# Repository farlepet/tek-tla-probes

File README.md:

Tektronix logic analyzer probes
===============================

This repo contains logic probes/leadsets for Tektronix logic analyzers, currently
specifically for the TLA 5200 series.

More details to come once I receive PCBs and build some probes.

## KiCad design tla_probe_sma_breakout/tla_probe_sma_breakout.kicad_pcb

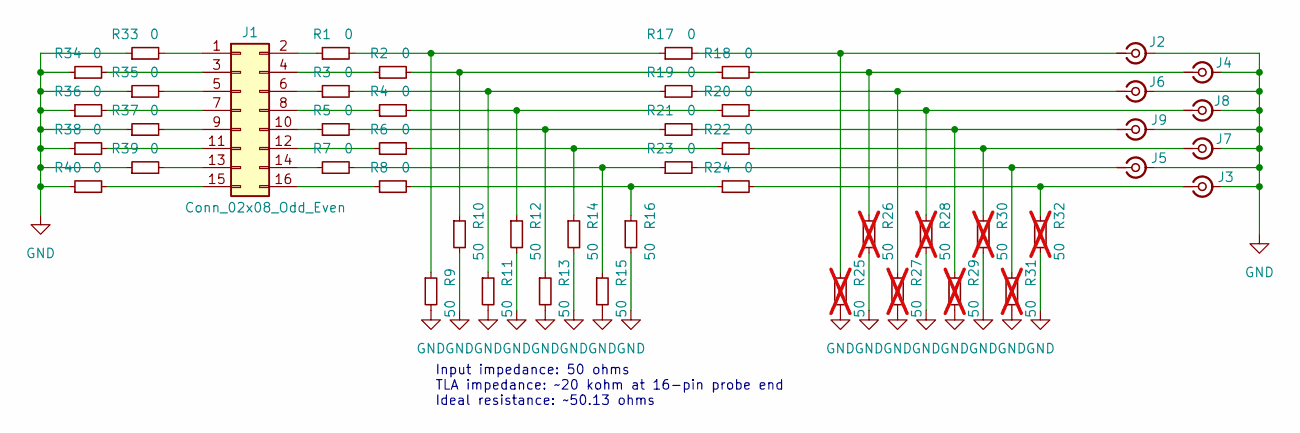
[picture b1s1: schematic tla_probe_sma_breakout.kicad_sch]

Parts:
J1: Conn_02x08_Odd_Even; PinHeader_2x08_P2.54mm_Vertical
J2, J3, J4, J5, J6, J7, J8, J9: Conn_Coaxial_Small; SMA Board Edge Jack
R1, R2, R3, R4, R5, R6, R7, R8, R17, R18, R19, R20, R21, R22, R23, R24, R33, R34, R35, R36, R37, R38, R39, R40: 0; R_0603_1608Metric
R9, R10, R11, R12, R13, R14, R15, R16: 50; R_0603_1608Metric
R25, R26, R27, R28, R29, R30, R31, R32: 50; R_0603_1608Metric; not fitted

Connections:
GND: J2.2 (Ext), J3.2 (Ext), J4.2 (Ext), J5.2 (Ext), J6.2 (Ext), J7.2 (Ext), J8.2 (Ext), J9.2 (Ext), R9.2, R10.2, R11.2, R12.2, R13.2, R14.2, R15.2, R16.2, R25.2, R26.2, R27.2, R28.2, R29.2, R30.2, R31.2, R32.2, R33.1, R34.1, R35.1, R36.1, R37.1, R38.1, R39.1, R40.1
unnamed: J1.1, R33.2
unnamed: J1.2, R1.1
unnamed: J1.3, R34.2
unnamed: J1.4, R2.1
unnamed: J1.5, R35.2
unnamed: J1.6, R3.1
unnamed: J1.7, R36.2
unnamed: J1.8, R4.1
unnamed: J1.9, R37.2
unnamed: J1.10, R5.1
unnamed: J1.11, R38.2
unnamed: J1.12, R6.1
unnamed: J1.13, R39.2
unnamed: J1.14, R7.1
unnamed: J1.15, R40.2
unnamed: J1.16, R8.1
unnamed: J2.1 (In), R17.2, R25.1
unnamed: J4.1 (In), R18.2, R26.1
unnamed: J6.1 (In), R19.2, R27.1
unnamed: J8.1 (In), R20.2, R28.1
unnamed: J9.1 (In), R21.2, R29.1
unnamed: J7.1 (In), R22.2, R30.1
unnamed: J5.1 (In), R23.2, R31.1
unnamed: J3.1 (In), R24.2, R32.1
unnamed: R1.2, R9.1, R17.1
unnamed: R2.2, R10.1, R18.1
unnamed: R3.2, R11.1, R19.1
unnamed: R4.2, R12.1, R20.1
unnamed: R5.2, R13.1, R21.1
unnamed: R6.2, R14.1, R22.1
unnamed: R7.2, R15.1, R23.1
unnamed: R8.2, R16.1, R24.1

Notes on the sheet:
Input impedance: 50 ohms TLA impedance: ~20 kohm at 16-pin probe end Ideal resistance: ~50.13 ohms

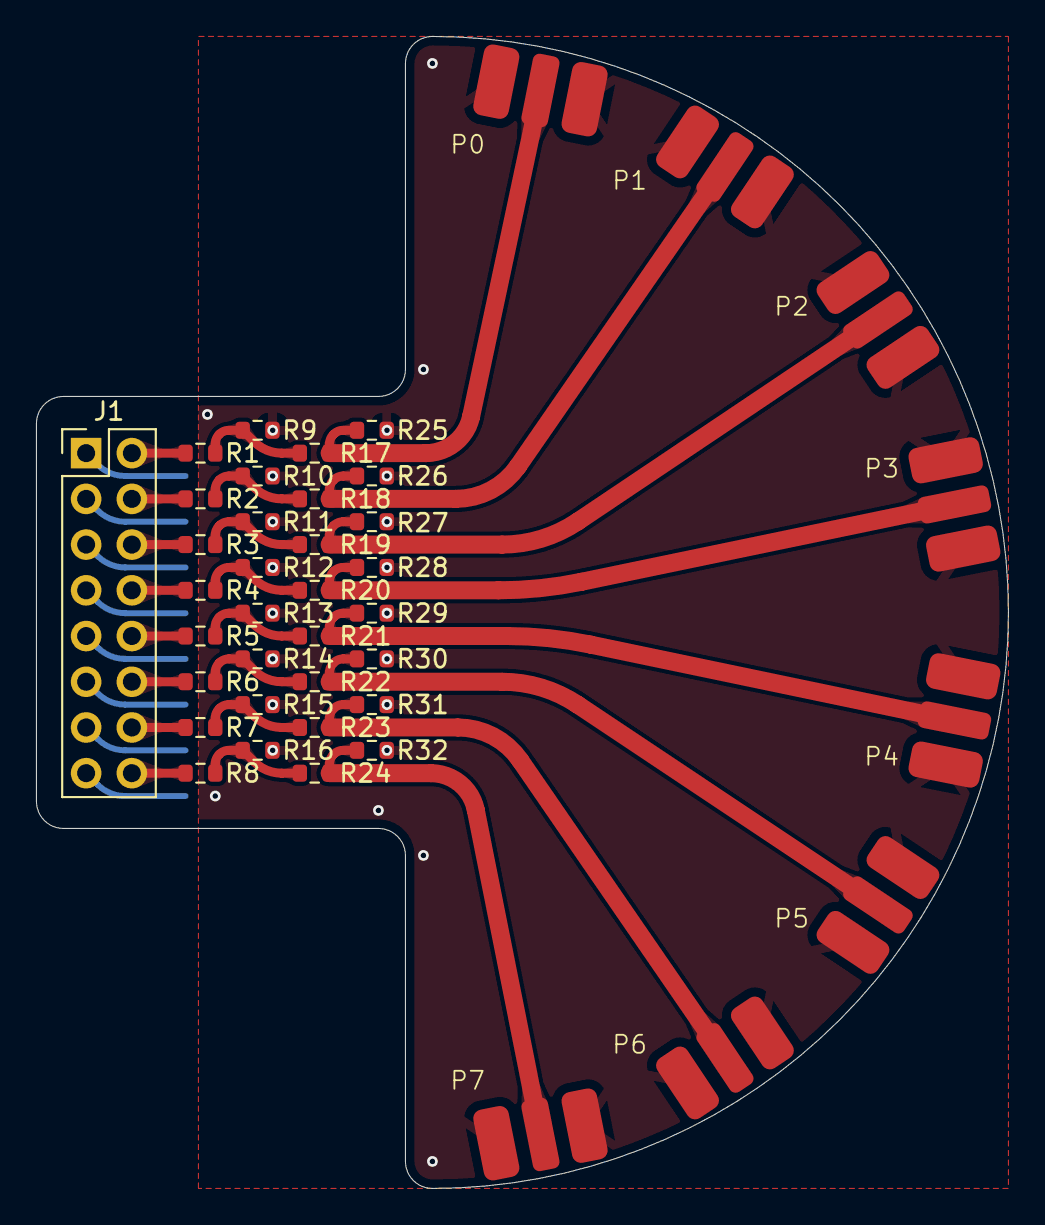
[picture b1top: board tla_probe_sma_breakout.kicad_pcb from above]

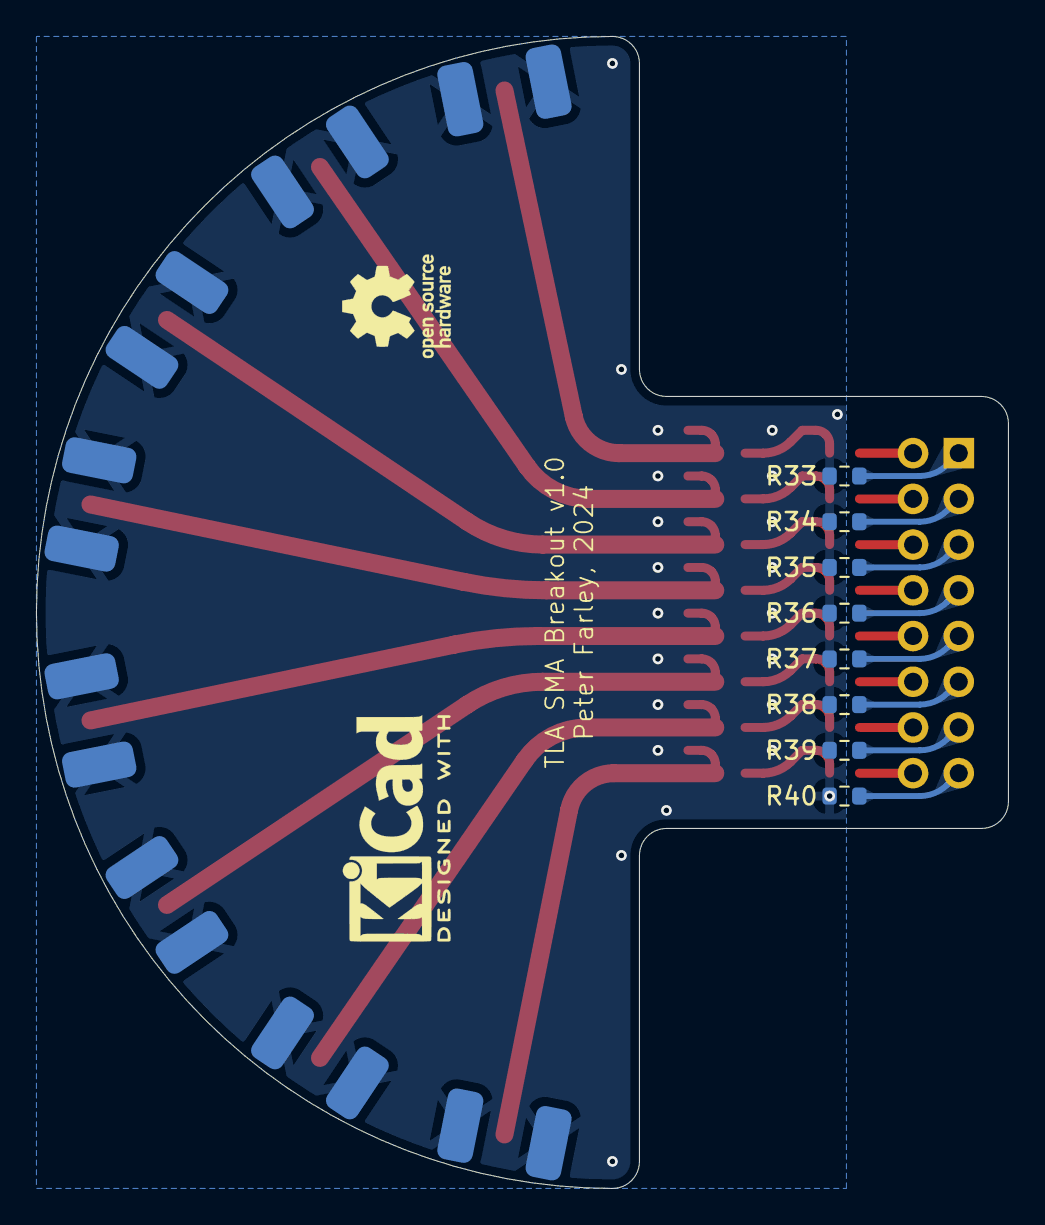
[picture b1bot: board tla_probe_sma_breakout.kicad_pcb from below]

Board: 2 copper layers, 54.0 x 64.0 mm, 49 parts (8 on the bottom side), 33 nets.

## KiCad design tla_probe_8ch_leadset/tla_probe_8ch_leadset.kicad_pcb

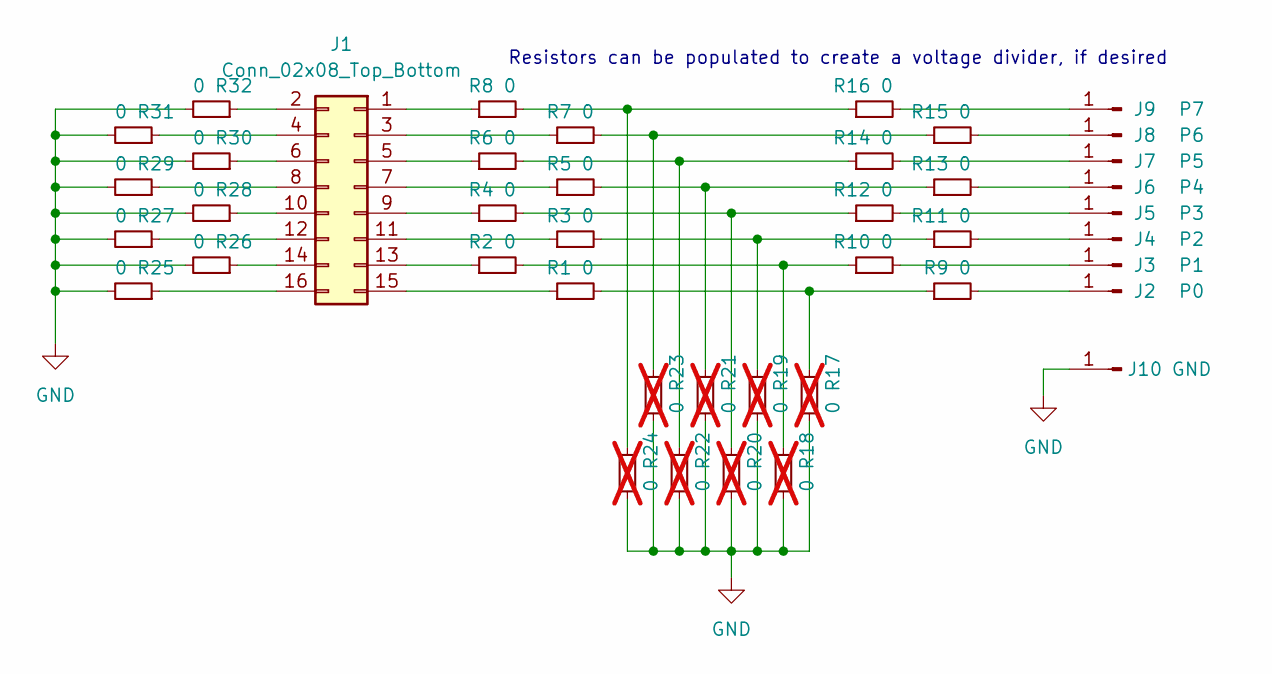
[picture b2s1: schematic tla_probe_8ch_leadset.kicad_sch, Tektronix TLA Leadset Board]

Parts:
J1: Conn_02x08_Top_Bottom; PinHeader_2x08_P2.54mm_Vertical
J2: P0; SolderWire-0.1sqmm_1x01_D0.4mm_OD1mm_Relief2x
J3: P1; SolderWire-0.1sqmm_1x01_D0.4mm_OD1mm_Relief2x
J4: P2; SolderWire-0.1sqmm_1x01_D0.4mm_OD1mm_Relief2x
J5: P3; SolderWire-0.1sqmm_1x01_D0.4mm_OD1mm_Relief2x
J6: P4; SolderWire-0.1sqmm_1x01_D0.4mm_OD1mm_Relief2x
J7: P5; SolderWire-0.1sqmm_1x01_D0.4mm_OD1mm_Relief2x
J8: P6; SolderWire-0.1sqmm_1x01_D0.4mm_OD1mm_Relief2x
J9: P7; SolderWire-0.1sqmm_1x01_D0.4mm_OD1mm_Relief2x
J10: GND; SolderWire-0.1sqmm_1x01_D0.4mm_OD1mm_Relief2x
R1, R2, R3, R4, R5, R6, R7, R8, R9, R10, R11, R12, R13, R14, R15, R16, R25, R26, R27, R28, R29, R30, R31, R32: 0; R_0603_1608Metric
R17, R18, R19, R20, R21, R22, R23, R24: 0; R_0603_1608Metric; not fitted

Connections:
GND: J10.1, R17.2, R18.2, R19.2, R20.2, R21.2, R22.2, R23.2, R24.2, R25.2, R26.2, R27.2, R28.2, R29.2, R30.2, R31.2, R32.2
unnamed: J1.1, R8.1
unnamed: J1.2, R32.1
unnamed: J1.3, R7.1
unnamed: J1.4, R31.1
unnamed: J1.5, R6.1
unnamed: J1.6, R30.1
unnamed: J1.7, R5.1
unnamed: J1.8, R29.1
unnamed: J1.9, R4.1
unnamed: J1.10, R28.1
unnamed: J1.11, R3.1
unnamed: J1.12, R27.1
unnamed: J1.13, R2.1
unnamed: J1.14, R26.1
unnamed: J1.15, R1.1
unnamed: J1.16, R25.1
unnamed: J9.1, R16.2
unnamed: J8.1, R15.2
unnamed: J7.1, R14.2
unnamed: J6.1, R13.2
unnamed: J5.1, R12.2
unnamed: J4.1, R11.2
unnamed: J3.1, R10.2
unnamed: J2.1, R9.2
unnamed: R5.2, R13.1, R21.1
unnamed: R3.2, R11.1, R19.1
unnamed: R1.2, R9.1, R17.1
unnamed: R8.2, R16.1, R24.1
unnamed: R6.2, R14.1, R22.1
unnamed: R4.2, R12.1, R20.1
unnamed: R2.2, R10.1, R18.1
unnamed: R7.2, R15.1, R23.1

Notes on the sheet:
Resistors can be populated to create a voltage divider, if desired

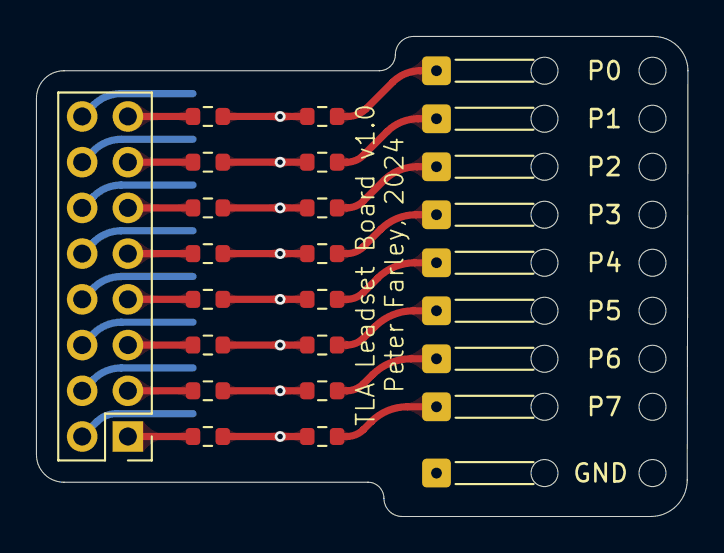
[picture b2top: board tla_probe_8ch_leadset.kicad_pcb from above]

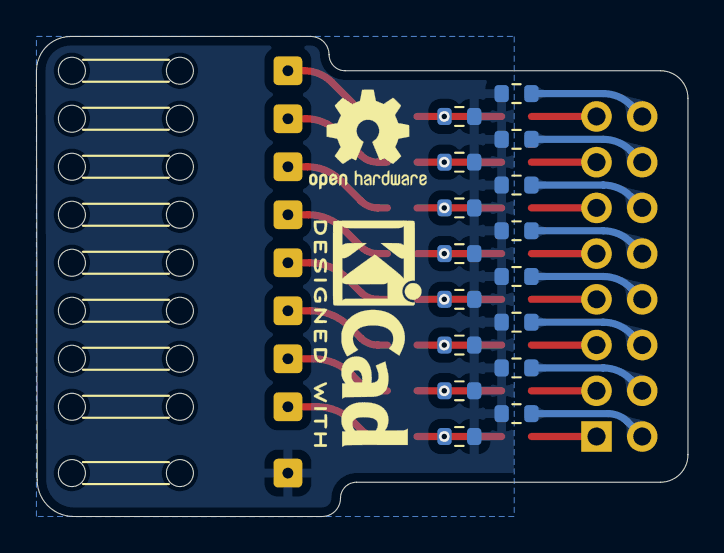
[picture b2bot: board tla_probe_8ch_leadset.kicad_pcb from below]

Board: 2 copper layers, 36.2 x 26.7 mm, 42 parts (16 on the bottom side), 33 nets.

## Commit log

2024-03-20 tla_probe_8ch_leadset rev 1.0
2024-03-20 Add P6417 retaining bracket model
    This is a simple 3D print that allows securing P6417 probes to the TLA,
    as the proper retaining brackets are not too common.
2024-07-02 Add enclosure
2024-07-20 Add prototype SMA breakout board
